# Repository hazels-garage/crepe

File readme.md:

# CREPE

## 40% ultrathin ortholinear keyboard

## MATERIALS
- 40x [Kailh X Switches](https://mkultra.click/kailh-x-switches-and-keycaps/)
- 40x [1N4148 - SOD-123 Diodes](https://mkultra.click/diode-1n4148-sod-123f/)
- 1x ProMicro style Microrocontroller (ProMicro, Nice!Nano, EliteC, STeMCell, etc)
- 1x [Power Switch](https://mkultra.click/alps-ssss811101/) (optional)
- 1x Battery (optional)

### PCB Render

## FIRMWARE

[QMK](https://github.com/jasonhazel/qmk_hazel/tree/master/keyboards/jasonhazel/crepe)

[ZMK](https://github.com/jasonhazel/zmk-config/tree/master/config/boards/shields/crepe)

## SUPPORT

<p xmlns:cc="http://creativecommons.org/ns#" xmlns:dct="http://purl.org/dc/terms/"><a property="dct:title" rel="cc:attributionURL" href="https://github.com/jasonhazel/crepe">CREPE</a> by <a rel="cc:attributionURL dct:creator" property="cc:attributionName" href="https://github.com/jasonhazel">Jason Hazel</a> is licensed under <a href="http://creativecommons.org/licenses/by/4.0/?ref=chooser-v1" target="_blank" rel="license noopener noreferrer" style="display:inline-block;">CC BY 4.0</a></p>

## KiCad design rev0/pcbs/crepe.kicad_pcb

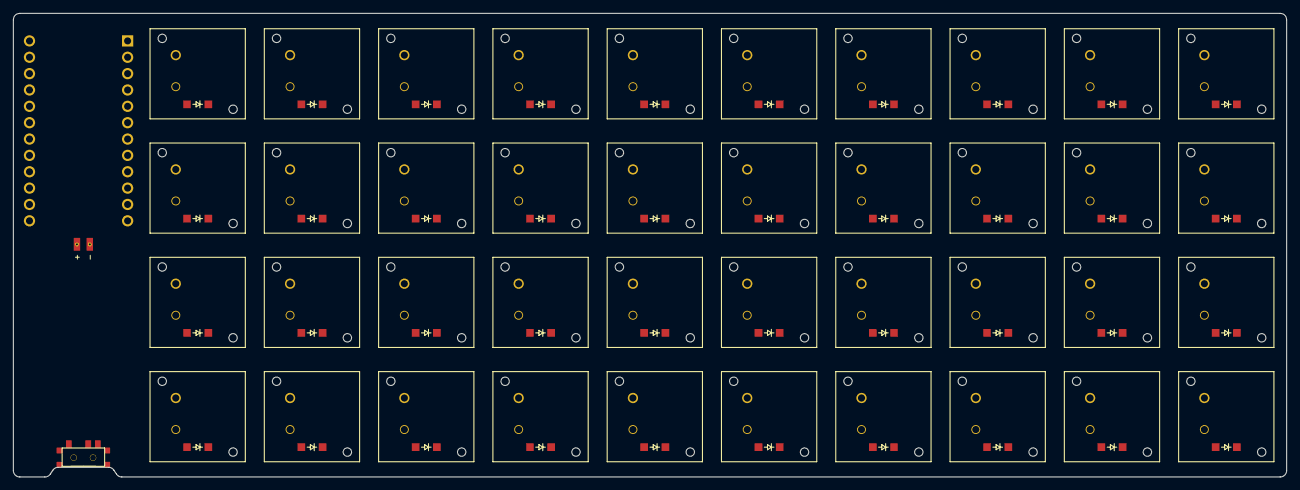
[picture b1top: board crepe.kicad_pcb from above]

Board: 2 copper layers, 197.8 x 72.0 mm, 83 parts (0 on the bottom side), 54 nets, no tracks yet.

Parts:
D1, D2, D3, D4, D5, D6, D7, D8, D9, D10, D11, D12, D13, D14, D15, D16, D17, D18, D19, D20, D21, D22, D23, D24, D25, D26, D27, D28, D29, D30, D31, D32, D33, D34, D35, D36, D37, D38, D39, D40: ComboDiode
PAD1, PAD2: SMDPad
S1, S2, S3, S4, S5, S6, S7, S8, S9, S10, S11, S12, S13, S14, S15, S16, S17, S18, S19, S20, S21, S22, S23, S24, S25, S26, S27, S28, S29, S30, S31, S32, S33, S34, S35, S36, S37, S38, S39, S40: Kailh-PG1425-X-Switch
T1: SPDT_C128955

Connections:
BAT: PAD2.1, T1.1
c0: S1.1, S2.1, S3.1, S4.1, S21.1, S22.1, S23.1, S24.1
c1: S5.1, S6.1, S7.1, S8.1, S25.1, S26.1, S27.1, S28.1
c2: S9.1, S10.1, S11.1, S12.1, S29.1, S30.1, S31.1, S32.1
c3: S13.1, S14.1, S15.1, S16.1, S33.1, S34.1, S35.1, S36.1
c4: S17.1, S18.1, S19.1, S20.1, S37.1, S38.1, S39.1, S40.1
index_bottom: D14.2, S14.2
index_extras: D13.2, S13.2
index_home: D15.2, S15.2
index_top: D16.2, S16.2
inner_bottom: D18.2, S18.2
inner_extras: D17.2, S17.2
inner_home: D19.2, S19.2
inner_top: D20.2, S20.2
middle_bottom: D10.2, S10.2
middle_extras: D9.2, S9.2
middle_home: D11.2, S11.2
middle_top: D12.2, S12.2
mirror_index_bottom: D34.2, S34.2
mirror_index_extras: D33.2, S33.2
mirror_index_home: D35.2, S35.2
mirror_index_top: D36.2, S36.2
mirror_inner_bottom: D38.2, S38.2
mirror_inner_extras: D37.2, S37.2
mirror_inner_home: D39.2, S39.2
mirror_inner_top: D40.2, S40.2
mirror_middle_bottom: D30.2, S30.2
mirror_middle_extras: D29.2, S29.2
mirror_middle_home: D31.2, S31.2
mirror_middle_top: D32.2, S32.2
mirror_pinky_bottom: D22.2, S22.2
mirror_pinky_extras: D21.2, S21.2
mirror_pinky_home: D23.2, S23.2
mirror_pinky_top: D24.2, S24.2
mirror_ring_bottom: D26.2, S26.2
mirror_ring_extras: D25.2, S25.2
mirror_ring_home: D27.2, S27.2
mirror_ring_top: D28.2, S28.2
pinky_bottom: D2.2, S2.2
pinky_extras: D1.2, S1.2
pinky_home: D3.2, S3.2
pinky_top: D4.2, S4.2
r0: D4.1, D8.1, D12.1, D16.1, D20.1
r1: D3.1, D7.1, D11.1, D15.1, D19.1
r2: D2.1, D6.1, D10.1, D14.1, D18.1
r3: D1.1, D5.1, D9.1, D13.1, D17.1
r4: D24.1, D28.1, D32.1, D36.1, D40.1
r5: D23.1, D27.1, D31.1, D35.1, D39.1
r6: D22.1, D26.1, D30.1, D34.1, D38.1
r7: D21.1, D25.1, D29.1, D33.1, D37.1
ring_bottom: D6.2, S6.2
ring_extras: D5.2, S5.2
ring_home: D7.2, S7.2
ring_top: D8.2, S8.2

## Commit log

2022-11-13 init
2022-11-13 groundfill
2022-11-13 rev0 finished
2022-11-13 move gerber to top
2022-11-13 forgot to save the kicad file
2022-11-13 cleaning up ergogen file
2022-11-13 adding qmk link
2022-11-13 add zmk link
2022-11-13 trying discord badge
2022-11-13 trying this one
2022-11-13 make clickable
2022-11-14 move link
2022-11-22 update image
2022-11-22 remove wip warning
2022-11-23 render previews
2022-11-23 Update gallery (automated)
2022-11-23 fix the path of the images
2022-11-23 rm the old stuff
2022-11-23 add auto render to readme
2022-11-23 dispatch workflow on pcb changes
2022-11-23 add bottom render
2026-03-26 Remove Hazel's Garage badge from README
    Removed badge for Hazel's Garage from README.

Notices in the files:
readme.md:
https://img.shields.io/github/license/hazels-garage/crepe?label=%20&logo=creativecommons&logoColor=%23ffffff&style=flat-square
